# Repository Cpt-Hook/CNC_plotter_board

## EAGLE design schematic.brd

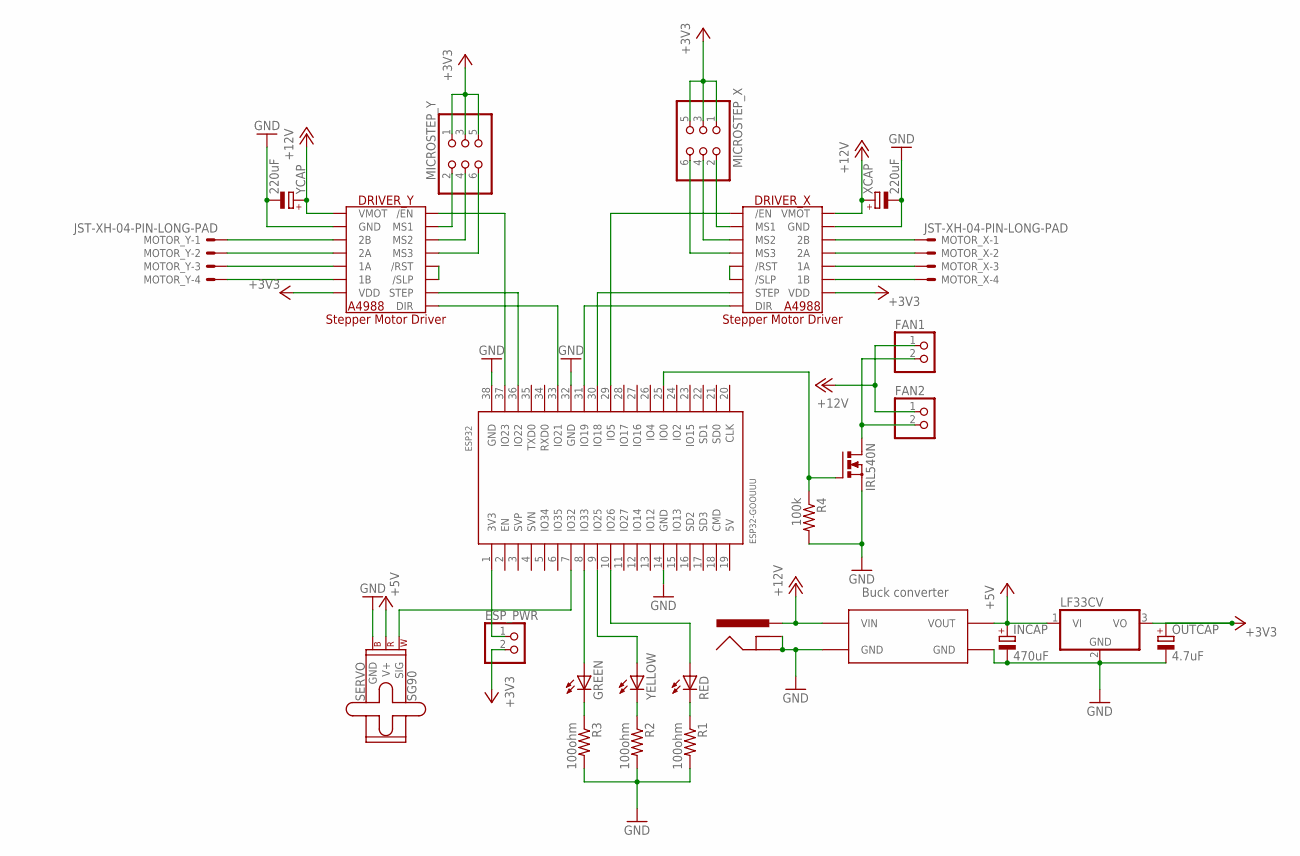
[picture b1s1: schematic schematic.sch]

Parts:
DRIVER_X: A4988_STEP
DRIVER_Y: A4988_STEP
ESP32: ESP32-GOOUUU; ESP32--GOOUUU
ESP_PWR: PINHD-1X2; 1X02
FAN1, FAN2: PINHD-1X2; 1X02
GREEN: LED5MM
INCAP: 470uF; E2,5RE
IRL540N: PMOSFET_NTO220BV; TO220BV
LF33CV: LF33CVTV; TO220V
MICROSTEP_X: PINHD-2X3; 2X03
MICROSTEP_Y: PINHD-2X3; 2X03
MOTOR_X: JST-XH-04-PIN-LONG-PAD; JST-XH-04-PACKAGE-LONG-PAD
MOTOR_Y: JST-XH-04-PIN-LONG-PAD; JST-XH-04-PACKAGE-LONG-PAD
OUTCAP: 4.7uF; E2,5RE
POWER_JACK: POWER_JACKPTH; POWER_JACK_PTH
R1, R2, R3: 100ohm; 0207/10
R4: 100k; 0207/10
RED: LED5MM
SG90: SERVO; 1X03
U$2: BUCK-CONVERTER
XCAP: 220uF; E2,5-6
YCAP: 220uF; E2,5-6
YELLOW: LED5MM

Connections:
1AX: DRIVER_X.1A, MOTOR_X.3
1AY: DRIVER_Y.1A, MOTOR_Y.3
1BX: DRIVER_X.1B, MOTOR_X.4
1BY: DRIVER_Y.1B, MOTOR_Y.4
2AX: DRIVER_X.2A, MOTOR_X.2
2AY: DRIVER_Y.2A, MOTOR_Y.2
2BX: DRIVER_X.2B, MOTOR_X.1
2BY: DRIVER_Y.2B, MOTOR_Y.1
+3V3: DRIVER_X.VDD, DRIVER_Y.VDD, ESP_PWR.2, LF33CV.3 (VO), MICROSTEP_X.1, MICROSTEP_X.3, MICROSTEP_X.5, MICROSTEP_Y.1, MICROSTEP_Y.3, MICROSTEP_Y.5, OUTCAP.+
+5V: INCAP.+, LF33CV.1 (VI), SG90.2 (V+), U$2.VOUT1 (VOUT), U$2.VOUT2 (VOUT)
+12V: DRIVER_X.VMOT, DRIVER_Y.VMOT, FAN1.1, FAN2.1, POWER_JACK.PWR, U$2.VIN1 (VIN), U$2.VIN2 (VIN), XCAP.+, YCAP.+
ESP_PWR: ESP32.1 (3V3), ESP_PWR.1
FAN_EN: ESP32.25 (IO0), IRL540N.G, R4.1
FAN_PW: FAN1.2, FAN2.2, IRL540N.D
GND: DRIVER_X.GND, DRIVER_X.GND2 (GND), DRIVER_Y.GND, DRIVER_Y.GND2 (GND), ESP32.14 (GND), ESP32.32 (GND), ESP32.38 (GND), INCAP.-, IRL540N.S, LF33CV.2 (GND), OUTCAP.-, POWER_JACK.GND, POWER_JACK.GND@1 (GND), R1.2, R2.2, R3.2, R4.2, SG90.3 (GND), U$2.GND@1 (GND), U$2.GND@2 (GND), U$2.GND@3 (GND), U$2.GND@4 (GND), XCAP.-, YCAP.-
GREEN_LED: ESP32.8 (IO33), GREEN.A
GREEN_R3: GREEN.K (C), R3.1
unnamed: DRIVER_Y.MS1, MICROSTEP_Y.2
unnamed: DRIVER_Y./RST, DRIVER_Y./SLP
unnamed: DRIVER_Y.MS2, MICROSTEP_Y.4
unnamed: DRIVER_Y.MS3, MICROSTEP_Y.6
unnamed: DRIVER_X.MS1, MICROSTEP_X.2
unnamed: DRIVER_X.MS2, MICROSTEP_X.4
unnamed: DRIVER_X.MS3, MICROSTEP_X.6
unnamed: DRIVER_X./RST, DRIVER_X./SLP
RED_LED: ESP32.10 (IO26), RED.A
RED_R1: R1.1, RED.K (C)
SERVO: ESP32.7 (IO32), SG90.1 (SIG)
X_DIR: DRIVER_X.DIR, ESP32.31 (IO19)
X_EN: DRIVER_X./EN, ESP32.29 (IO5)
X_STEP: DRIVER_X.STEP, ESP32.30 (IO18)
YELLOW_LED: ESP32.9 (IO25), YELLOW.A
YELLOW_R2: R2.1, YELLOW.K (C)
Y_DIR: DRIVER_Y.DIR, ESP32.33 (IO21)
Y_EN: DRIVER_Y./EN, ESP32.37 (IO23)
Y_STEP: DRIVER_Y.STEP, ESP32.36 (IO22)

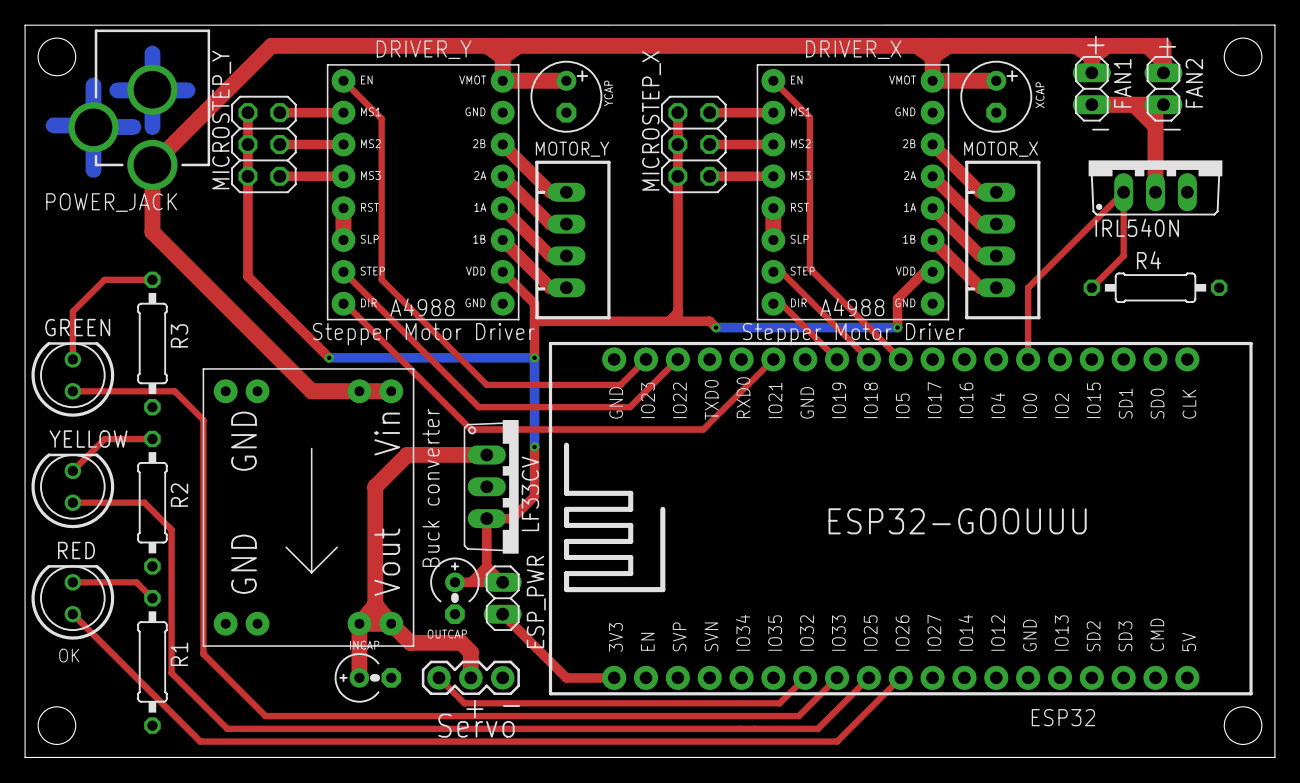
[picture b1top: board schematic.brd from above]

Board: 2 copper layers, 99.7 x 58.4 mm, 26 parts (0 on the bottom side), 36 nets.

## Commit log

2019-02-20 akjdf;sjf
2019-02-20 kasjf;lkdsjf
2019-02-20 kasdfj
2019-02-21 adefd
2019-02-21 Final commit - board ordered with this design

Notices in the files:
parts and their libraries:
SparkFun-Electromechanical: Licensing: Creative Commons ShareAlike 4.0 International - https://creativecommons.org/licenses/by-sa/4.0
